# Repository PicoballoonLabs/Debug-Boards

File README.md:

# Debug-Boards

This repository contains the hardware designs for our integrated debug probe, debug adapter, flex debug cables and RF calibration board.

## 📦 Contents

This repository includes designs for:

*   **Flex debug cable**: Flexible flat cable that connects a debugger to the low-profile debug connector on the target board.
*   **Debug Adapter**: SWD debug adapter board that breaks the target debug connector out to a standard debug host, with its own target power supply.
*   **Integrated Debugger**: Integrated debug probe for flashing and debugging target hardware over SWD, with a UART bridge and switchable target power. It is hardware compatible with the [Black Magic Debug](https://black-magic.org/) firmware.
*   **RF VNA calibrator**: Calibration board for vector network analyzer (VNA) RF measurements.

Each subdirectory is a standalone KiCad project with its schematics and PCB layout, and a `production` folder with the manufacturing files (gerbers, BOM, pick-and-place positions) of the released revisions.

The projects use the symbol, footprint and 3D model libraries from [Hardware-Resources](https://github.com/PicoballoonLabs/Hardware-Resources).

## 🔌 Integrated Debugger firmware

No firmware is distributed in this repository. The Integrated Debugger runs the upstream [Black Magic Debug](https://github.com/blackmagic-debug/blackmagic) firmware (GPLv3), which can be installed and updated with [bmputil](https://github.com/blackmagic-debug/bmputil).

The hardware designs in this repository are original work, released under the MIT Licence (see [LICENSE](LICENSE)). They are compatible with Black Magic Debug firmware but are not derived from it.

## 📄 Licence

The hardware designs in this repository are released under the MIT Licence, see [LICENSE](LICENSE).

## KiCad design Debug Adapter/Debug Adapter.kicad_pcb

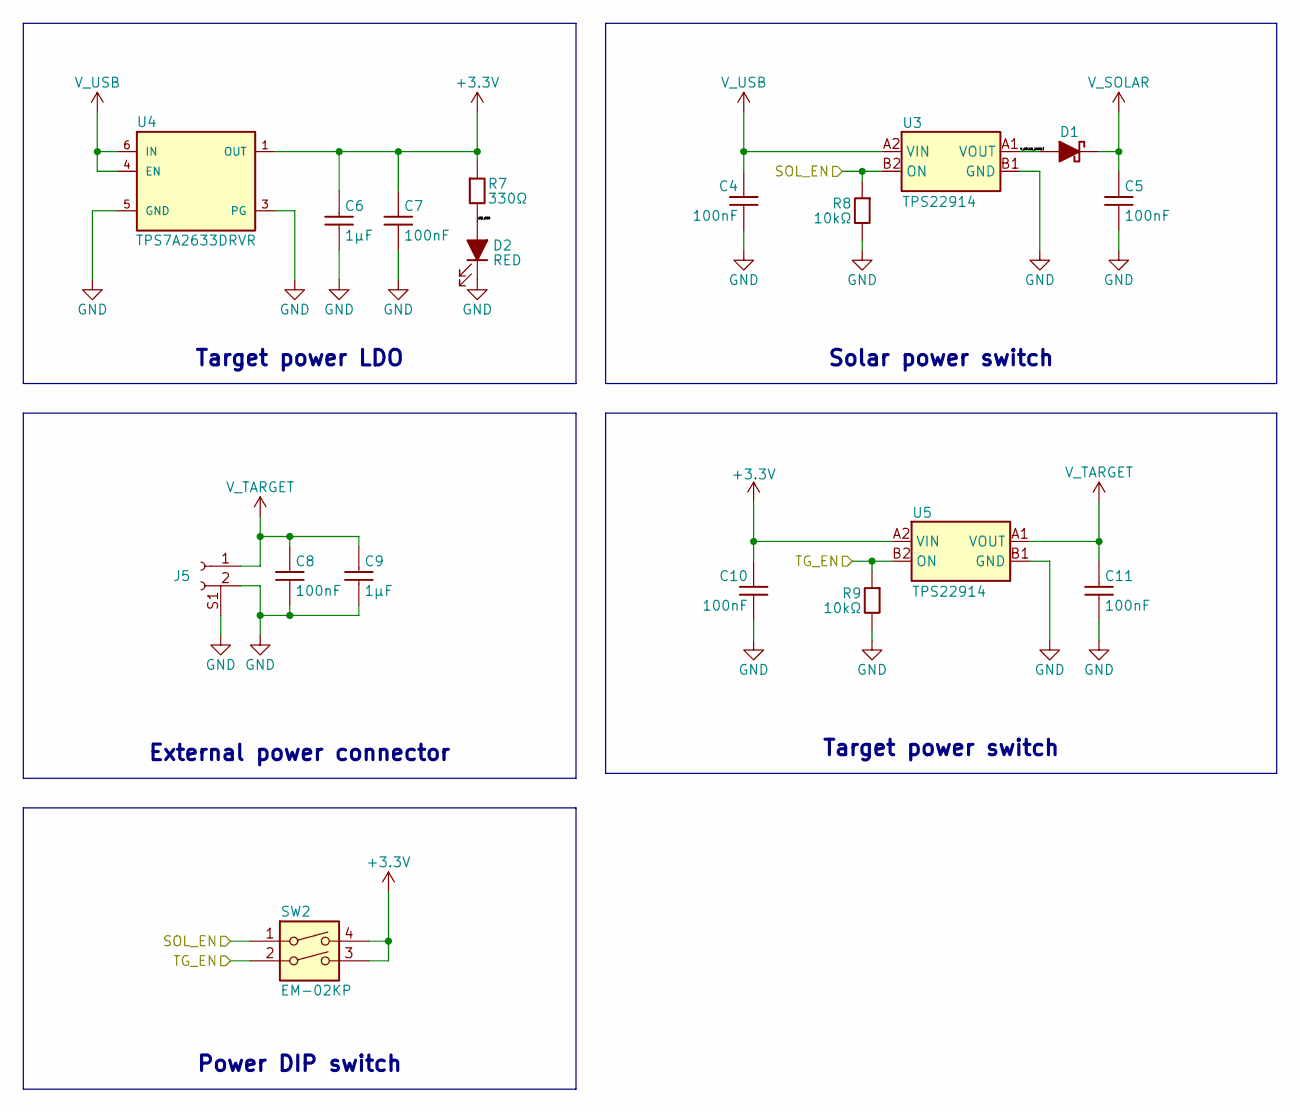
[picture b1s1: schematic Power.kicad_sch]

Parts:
C4, C5, C8, C10, C11: 100nF; Capacitor 0201; MPN GRM033R61A104KE15D; JLCPCB Part # C76934
C6, C9: 1μF; Capacitor 0201; MPN GRM033R60J105MEA2D; JLCPCB Part # C76930
C7: 100nF; Capacitor 0201; MPN GRM033R61A104KE15D; LCSC Part # C76934
D1: PMEG3005EL,315; Diode SOD-882; MPN PMEG3005EL,315; JLCPCB Part # C282565
D2: RED; LED 0603; MPN XL-1608SURC-06; LCSC Part # C965799
J5: PWR; MOLEX 532610271; MPN 532610271; LCSC Part # C177225
R7: 330Ω; Resistor 0201; MPN ERJ1GNF3300C; LCSC Part # C713496
R8, R9: 10kΩ; Resistor 0201; MPN ERJ1GNF1002C; JLCPCB Part # C717002
SW2: EM-02KP; MPN EM-02KP; LCSC Part # C129078
U3, U5: TPS22914; DSBGA-4; MPN TPS22914BYFPR; JLCPCB Part # C1848394
U4: TPS7A2633DRVR; WSON-6 2x2mm; MPN TPS7A2633DRVR; LCSC Part # C2876256

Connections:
+3.3V: C6.1, C7.1, C10.1, R7.1, SW2.3, SW2.4, U4.1 (OUT), U5.A2 (VIN); also elsewhere on the board
/Host/SOL_EN: R8.1, SW2.1, U3.B2 (ON); also elsewhere on the board
/Host/TG_EN: R9.1, SW2.2, U5.B2 (ON); also elsewhere on the board
/Power/LED_REG: D2.1 (K), R7.2
/Power/V_SOLAR_UNFILT: D1.2 (A), U3.A1 (VOUT)
GND: C4.2, C5.2, C6.2, C7.2, C8.2, C9.2, C10.2, C11.2, D2.2 (A), J5.2, J5.S1, J5.S2, R8.2, R9.2, U3.B1 (GND), U4.3 (PG), U4.5 (GND), U4.7 (EXP), U5.B1 (GND); also elsewhere on the board
V_SOLAR: C5.1, D1.1 (K); also elsewhere on the board
V_TARGET: C8.1, C9.1, C11.1, J5.1, U5.A1 (VOUT); also elsewhere on the board
V_USB: C4.1, U3.A2 (VIN), U4.4 (EN), U4.6 (IN); also elsewhere on the board

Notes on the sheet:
Power DIP switch
Target power switch
Solar power switch
External power connector
Target power LDO

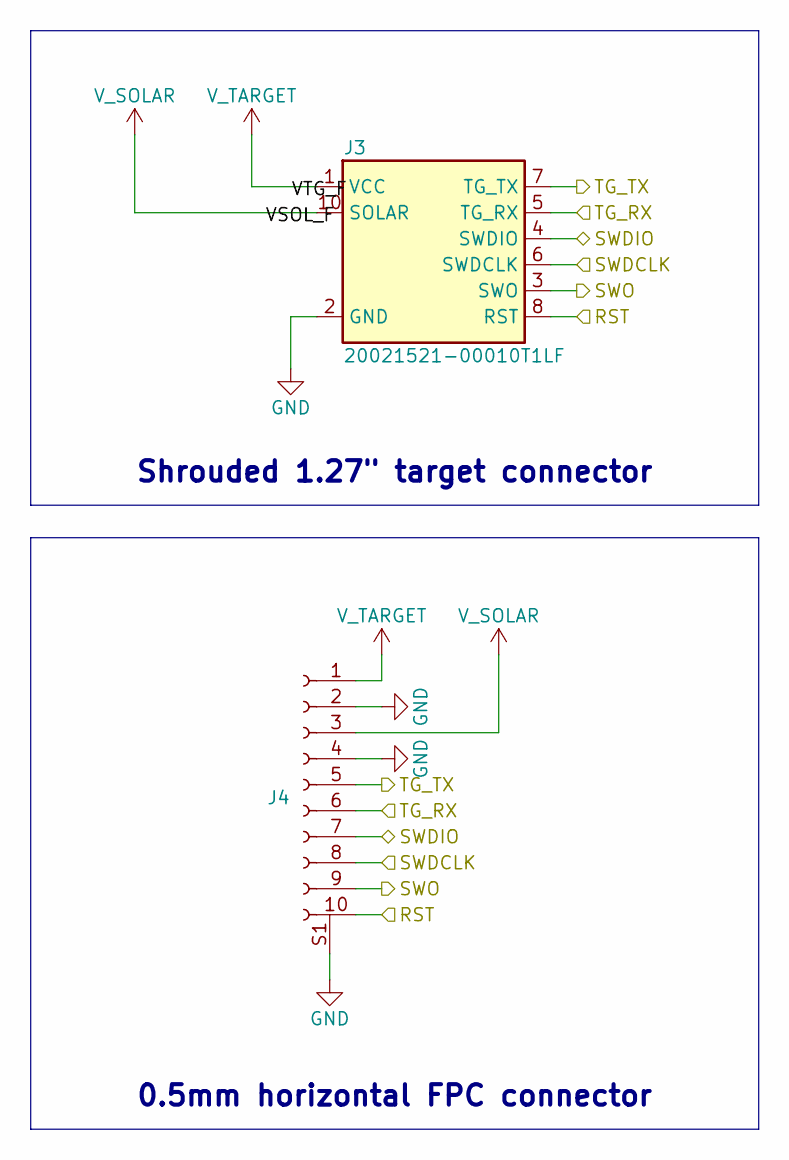
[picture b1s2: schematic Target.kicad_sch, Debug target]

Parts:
J3: 20021521-00010T1LF; MPN 20021521-00010T1LF; LCSC Part # C2972785
J4: FPC socket 10P; FPC connector FPC-05F-10PH20; MPN FPC-05F-10PH20; LCSC Part # C2856798

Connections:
/Host/DEBUG_RX: J3.7 (TG_TX), J4.5; also elsewhere on the board
/Host/DEBUG_TX: J3.5 (TG_RX), J4.6; also elsewhere on the board
/Host/RST: J3.8 (RST), J4.10; also elsewhere on the board
/Host/SWDCLK: J3.6 (SWDCLK), J4.8; also elsewhere on the board
/Host/SWDIO: J3.4 (SWDIO), J4.7; also elsewhere on the board
/Host/SWO: J3.3 (SWO), J4.9; also elsewhere on the board
GND: J3.2 (GND), J3.9 (GND), J4.2, J4.4, J4.S1, J4.S2; also elsewhere on the board
V_SOLAR: J3.10 (SOLAR), J4.3; also elsewhere on the board
V_TARGET: J3.1 (VCC), J4.1; also elsewhere on the board

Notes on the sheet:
Shrouded 1.27{dblquote} target connector
0.5mm horizontal FPC connector

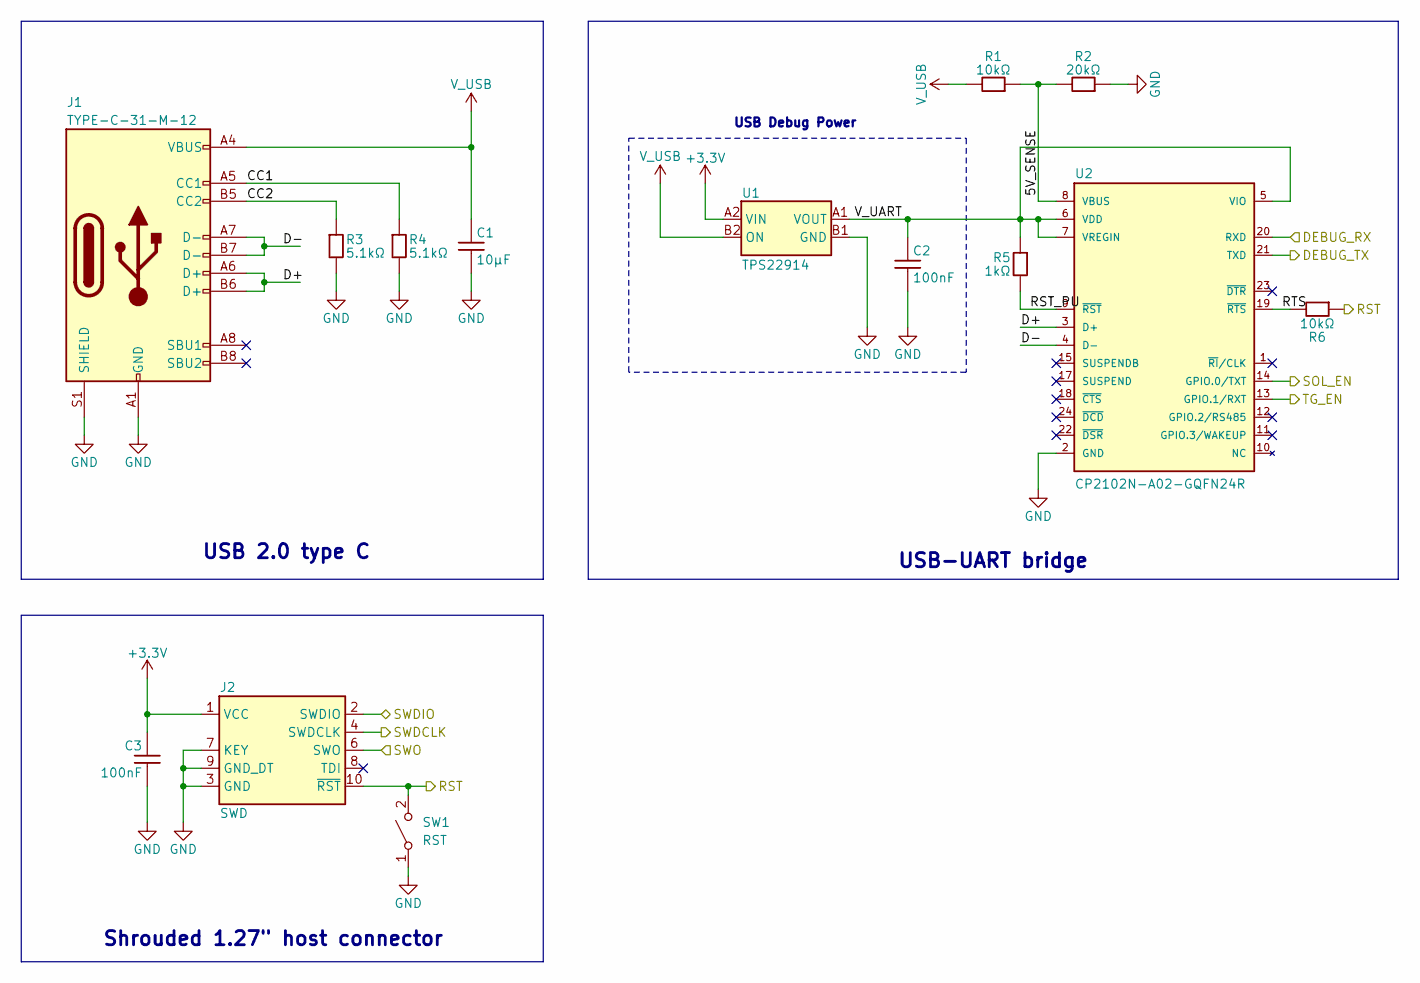
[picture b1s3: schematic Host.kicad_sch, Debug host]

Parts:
C1: 10μF; Capacitor 0402; MPN GRM155R60J106ME44D; JLCPCB Part # C76991
C2, C3: 100nF; Capacitor 0201; MPN GRM033R61A104KE15D; JLCPCB Part # C76934
J1: TYPE-C-31-M-12; MPN TYPE-C-31-M-12; JLCPCB Part # C165948
J2: SWD; 20021521-00010T1LF; MPN 20021521-00010T1LF; LCSC Part # C2972785
R1, R6: 10kΩ; Resistor 0201; MPN ERJ1GNF1002C; JLCPCB Part # C717002
R2: 20kΩ; Resistor 0201; MPN RC0201FR-0720KL; JLCPCB Part # C295787
R3, R4: 5.1kΩ; Resistor 0201; MPN RC0201FR-075K1L; JLCPCB Part # C274341
R5: 1kΩ; Resistor 0201; MPN ERJ1GNF1001C; JLCPCB Part # C717001
SW1: RST; Button GT-TC029B-H025-L1N; MPN GT-TC029B-H025-L1N; LCSC Part # C843669
U1: TPS22914; DSBGA-4; MPN TPS22914BYFPR; JLCPCB Part # C1848394
U2: CP2102N-A02-GQFN24R; QFN-24 4x4mm; MPN CP2102N-A02-GQFN24R; JLCPCB Part # C969151

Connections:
+3.3V: C3.1, J2.1 (VCC), U1.A2 (VIN); also elsewhere on the board
/Host/5V_SENSE: R1.1, R2.2, U2.8 (VBUS)
/Host/CC1: J1.A5 (CC1), R4.1
/Host/CC2: J1.B5 (CC2), R3.1
/Host/D+: J1.A6 (D+), J1.B6 (D+), U2.3 (D+)
/Host/D-: J1.A7 (D-), J1.B7 (D-), U2.4 (D-)
/Host/DEBUG_RX: U2.20 (RXD); also elsewhere on the board
/Host/DEBUG_TX: U2.21 (TXD); also elsewhere on the board
/Host/RST: J2.10 (~RST), R6.1, SW1.2 (B); also elsewhere on the board
/Host/RST_PU: R5.2, U2.9 (~RST)
/Host/RTS: R6.2, U2.19 (~RTS)
/Host/SOL_EN: U2.14 (GPIO.0/TXT); also elsewhere on the board
/Host/SWDCLK: J2.4 (SWDCLK); also elsewhere on the board
/Host/SWDIO: J2.2 (SWDIO); also elsewhere on the board
/Host/SWO: J2.6 (SWO); also elsewhere on the board
/Host/TG_EN: U2.13 (GPIO.1/RXT); also elsewhere on the board
/Host/V_UART: C2.1, R5.1, U1.A1 (VOUT), U2.5 (VIO), U2.6 (VDD), U2.7 (VREGIN)
GND: C1.2, C2.2, C3.2, J1.A1 (GND), J1.A12 (GND), J1.B1 (GND), J1.B12 (GND), J1.S1 (SHIELD), J1.S2 (SHIELD), J1.S3 (SHIELD), J1.S4 (SHIELD), J2.3 (GND), J2.5 (GND), J2.7 (KEY), J2.9 (GND_DT), R2.1, R3.2, R4.2, SW1.1 (A), U1.B1 (GND), U2.2 (GND), U2.25 (GND); also elsewhere on the board
V_USB: C1.1, J1.A4 (VBUS), J1.A9 (VBUS), J1.B4 (VBUS), J1.B9 (VBUS), R1.2, U1.B2 (ON); also elsewhere on the board

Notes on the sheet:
USB-UART bridge
Shrouded 1.27{dblquote} host connector
USB Debug Power
USB 2.0 type C

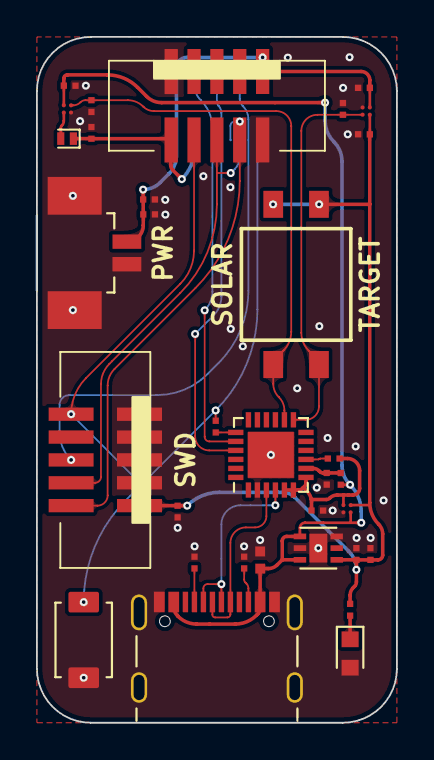
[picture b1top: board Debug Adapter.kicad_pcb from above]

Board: 2 copper layers, 20.0 x 38.1 mm, 34 parts (1 on the bottom side), 23 nets.

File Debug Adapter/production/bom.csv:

Designator,Footprint,Quantity,Value,LCSC Part #
C1,Capacitor 0402,1,10μF,C76991
"C10, C11, C2, C3, C4, C5, C7, C8",Capacitor 0201,8,100nF,C76934
"C6, C9",Capacitor 0201,2,1μF,C76930
D1,Diode SOD-882,1,"PMEG3005EL,315",C282565
D2,LED 0603,1,RED,C965799
J1,TYPE-C-31-M-12,1,TYPE-C-31-M-12,C165948
J2,20021521-00010T1LF,1,SWD,C2972785
J3,20021521-00010T1LF,1,20021521-00010T1LF,C2972785
J4,FPC connector FPC-05F-10PH20,1,FPC socket 10P,C2856798
J5,MOLEX 532610271,1,PWR,C177225
"R1, R6, R8, R9",Resistor 0201,4,10kΩ,C717002
R2,Resistor 0201,1,20kΩ,C295787
"R3, R4",Resistor 0201,2,5.1kΩ,C274341
R5,Resistor 0201,1,1kΩ,C717001
R7,Resistor 0201,1,330Ω,C713496
SW1,Button GT-TC029B-H025-L1N,1,RST,C843669
SW2,EM-02KP,1,EM-02KP,C129078
"U1, U3, U5",DSBGA-4,3,TPS22914,C1848394
U2,QFN-24 4x4mm,1,CP2102N-A02-GQFN24R,C969151
U4,WSON-6 2x2mm,1,TPS7A2633DRVR,C2876256

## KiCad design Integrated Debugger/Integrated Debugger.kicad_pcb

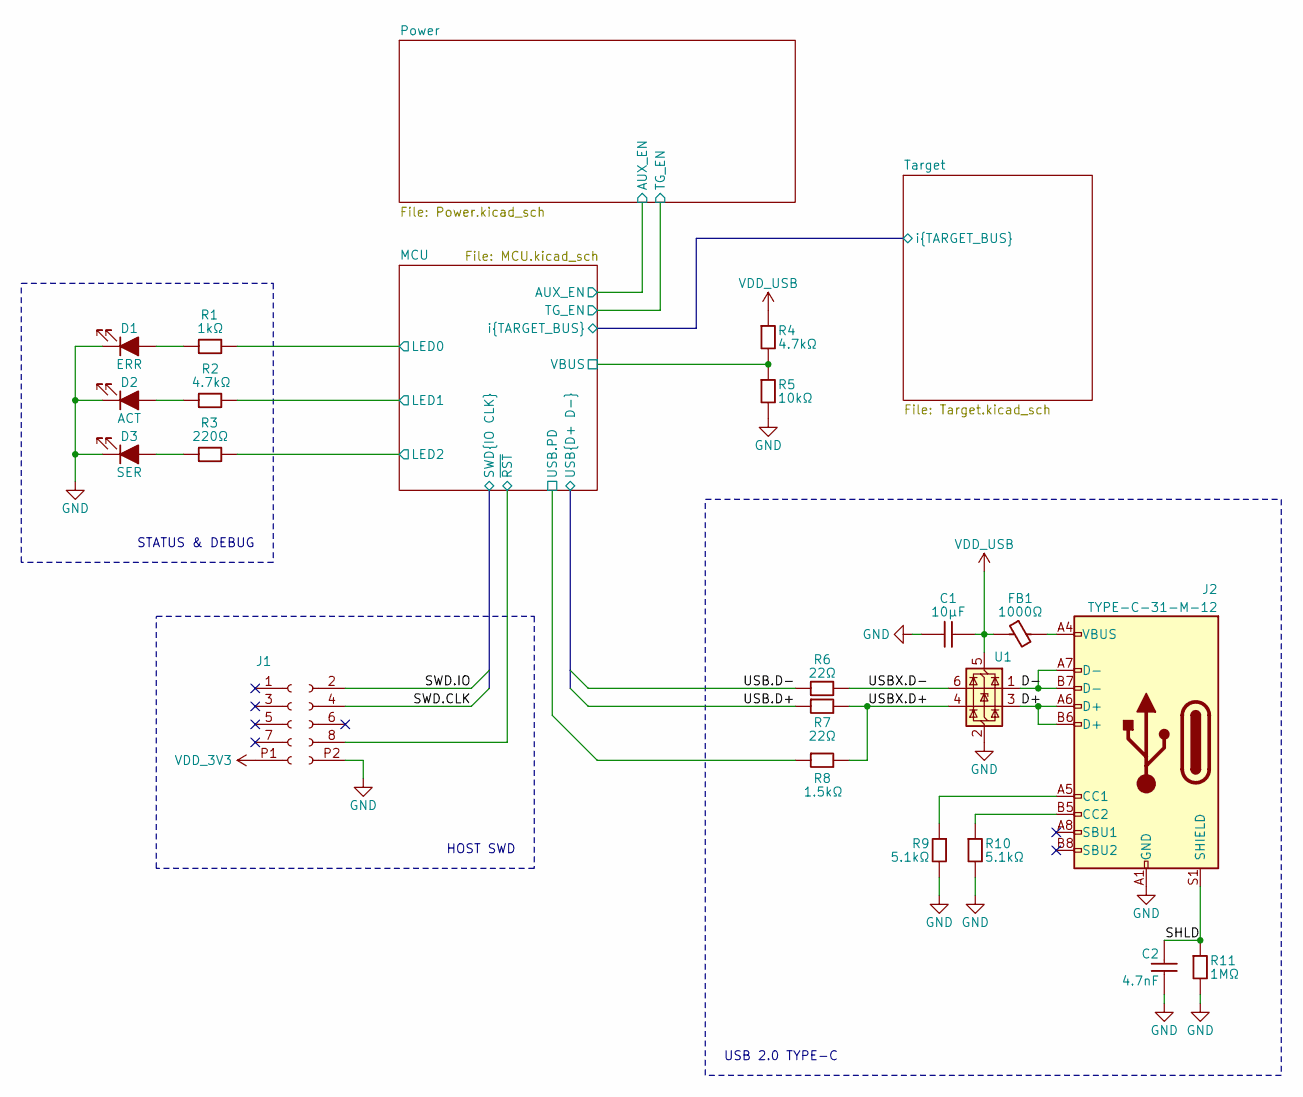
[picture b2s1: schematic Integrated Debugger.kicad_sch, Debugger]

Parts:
C1: 10μF; Capacitor 0402; MPN CL05A106MP5NUNC; LCSC Part # C315248
C2: 4.7nF; Capacitor 0603; MPN CC0603KRX7RABB472; LCSC Part # C596328
D1: ERR; LED 0402; MPN APHHS1005SURCK; LCSC Part # C2852592
D2: ACT; LED 0402; MPN APHHS1005LZGCK-V; LCSC Part # C5875752
D3: SER; LED 0402; MPN APHHS1005LQBC/D-V; LCSC Part # C5354973
FB1: 1000Ω; Inductor 0402; MPN BLM15HD102SN1D; LCSC Part # C21516
J1: B2B GT-B0353FSV06-08B0201; B2B GT-B0353MSV04-08B0201; MPN GT-B0353MSV04-08B0201; LCSC Part # C42385857
J2: TYPE-C-31-M-12; MPN TYPE-C-31-M-12; LCSC Part # C165948
R1: 1kΩ; Resistor 0201; MPN RC0201FR-071KL; LCSC Part # C138165
R2, R4: 4.7kΩ; Resistor 0201; MPN RC0201FR-074K7L; LCSC Part # C138135
R3: 220Ω; Resistor 0201; MPN AC0201JR-07220RL; LCSC Part # C226657
R5: 10kΩ; Resistor 0201; MPN ERJ1GNF1002C; LCSC Part # C717002
R6, R7: 22Ω; Resistor 0201; MPN RC0201FR-0722RL; LCSC Part # C155743
R8: 1.5kΩ; Resistor 0201; MPN RC0201FR-071K5L; LCSC Part # C155737
R9, R10: 5.1kΩ; Resistor 0201; MPN 0201WMF5101TEE; LCSC Part # C270344
R11: 1MΩ; Resistor 0603; MPN ESR03EZPJ105; LCSC Part # ESR03EZPJ105
U1: USBLC6-2P6; XSON-6; MPN USBULC6-2M6; LCSC Part # C2999115

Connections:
/D+: J2.A6 (D+), J2.B6 (D+), U1.3 (I/O2)
/D-: J2.A7 (D-), J2.B7 (D-), U1.1 (I/O1)
/MCU/LED0: R1.2; also elsewhere on the board
/MCU/LED1: R2.2; also elsewhere on the board
/MCU/LED2: R3.2; also elsewhere on the board
/MCU/SWD.CLK: J1.4; also elsewhere on the board
/MCU/SWD.IO: J1.2; also elsewhere on the board
/MCU/USB.D+: R7.1; also elsewhere on the board
/MCU/USB.D-: R6.1; also elsewhere on the board
/MCU/USB.PD: R8.1; also elsewhere on the board
/MCU/VBUS: R4.2, R5.1; also elsewhere on the board
/MCU/~RST: J1.8; also elsewhere on the board
/SHLD: C2.1, J2.S1 (SHIELD), J2.S2 (SHIELD), J2.S3 (SHIELD), J2.S4 (SHIELD), R11.1
/USBX.D+: R7.2, R8.2, U1.4 (I/O2)
/USBX.D-: R6.2, U1.6 (I/O1)
GND: C1.2, C2.2, D1.2 (A), D2.2 (A), D3.2 (A), J1.P2 (Pin_10), J1.P2_2 (Pin_10), J2.A1 (GND), J2.A12 (GND), J2.B1 (GND), J2.B12 (GND), R5.2, R9.2, R10.2, R11.2, U1.2 (GND); also elsewhere on the board
unnamed: D1.1 (K), R1.1
unnamed: D2.1 (K), R2.1
unnamed: D3.1 (K), R3.1
unnamed: FB1.2, J2.A4 (VBUS), J2.A9 (VBUS), J2.B4 (VBUS), J2.B9 (VBUS)
unnamed: J2.A5 (CC1), R9.1
unnamed: J2.B5 (CC2), R10.1
VDD_3V3: J1.P1 (Pin_9), J1.P1_2 (Pin_9); also elsewhere on the board
VDD_USB: C1.1, FB1.1, R4.1, U1.5 (VBUS); also elsewhere on the board

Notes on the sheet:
USB 2.0 TYPE-C
HOST SWD
STATUS & DEBUG

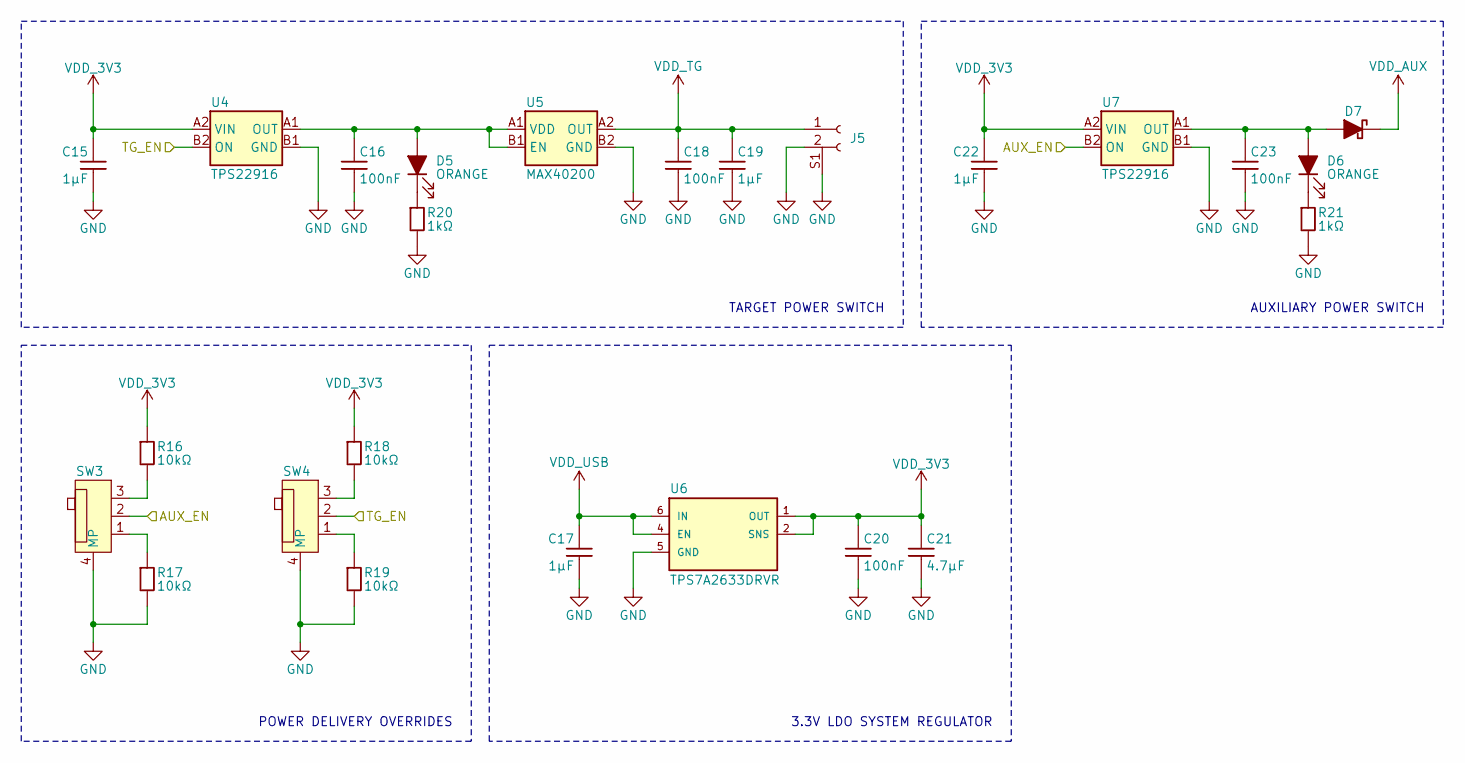
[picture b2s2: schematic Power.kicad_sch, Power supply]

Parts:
C15, C22: 1µF; Capacitor 0201; MPN GRM033R61C105ME15D; LCSC Part # C335102
C16, C18, C20, C23: 100nF; Capacitor 0201; MPN GRM033R6YA104KE14D; LCSC Part # C181043
C17, C19: 1μF; Capacitor 0201; MPN GRM033R61C105ME15D; LCSC Part # C335102
C21: 4.7μF; Capacitor 0201; MPN GRM035R60J475ME15D; LCSC Part # C335103
D5, D6: ORANGE; LED 0402; MPN APHHS1005SECK; LCSC Part # C5875753
D7: CFSH05-20L TR PBFREE; Diode SOD-882; MPN CFSH05-20L TR PBFREE; LCSC Part # C5258921
J5: PWR; JST-SH-2P; MPN SM02B-SRSS-TB(LF)(SN); LCSC Part # C160402
R16, R17, R18, R19: 10kΩ; Resistor 0201; MPN ERJ1GNF1002C; LCSC Part # C717002
R20, R21: 1kΩ; Resistor 0201; MPN RC0201FR-071KL; LCSC Part # C138165
SW3: AUXILIARY POWER; Switch MINI MSK12CO2; MPN MINI MSK12CO2; LCSC Part # C2681570
SW4: Target Override; Switch MINI MSK12CO2; MPN MINI MSK12CO2; LCSC Part # C2681570
U4, U7: TPS22916; DSBGA-4; MPN TPS22916CNLYFPR; LCSC Part # C3230035
U5: MAX40200; WLP-4; MPN MAX40200ANS+T; LCSC Part # C3227637
U6: TPS7A2633DRVR; WSON-6 2x2mm; MPN TLV76733DRVR; LCSC Part # C2848334

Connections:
/MCU/AUX_EN: SW3.2, U7.B2 (ON); also elsewhere on the board
/MCU/TG_EN: SW4.2, U4.B2 (ON); also elsewhere on the board
GND: C15.2, C16.2, C17.2, C18.2, C19.2, C20.2, C21.2, C22.2, C23.2, J5.2, J5.S1, J5.S2, R17.2, R19.2, R20.2, R21.2, SW3.4 (MP), SW4.4 (MP), U4.B1 (GND), U5.B2 (GND), U6.3 (GND), U6.5 (GND), U6.7 (EXP), U7.B1 (GND); also elsewhere on the board
unnamed: D5.2 (A), R20.1
unnamed: C16.1, D5.1 (K), U4.A1 (OUT), U5.A1 (VDD), U5.B1 (EN)
unnamed: D6.2 (A), R21.1
unnamed: C23.1, D6.1 (K), D7.2 (A), U7.A1 (OUT)
unnamed: R16.2, SW3.3
unnamed: R17.1, SW3.1
unnamed: R18.2, SW4.3
unnamed: R19.1, SW4.1
VDD_3V3: C15.1, C20.1, C21.1, C22.1, R16.1, R18.1, U4.A2 (VIN), U6.1 (OUT), U6.2 (SNS), U7.A2 (VIN); also elsewhere on the board
VDD_AUX: D7.1 (K); also elsewhere on the board
VDD_TG: C18.1, C19.1, J5.1, U5.A2 (OUT); also elsewhere on the board
VDD_USB: C17.1, U6.4 (EN), U6.6 (IN); also elsewhere on the board

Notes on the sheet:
POWER DELIVERY OVERRIDES
AUXILIARY POWER SWITCH
TARGET POWER SWITCH
3.3V LDO SYSTEM REGULATOR

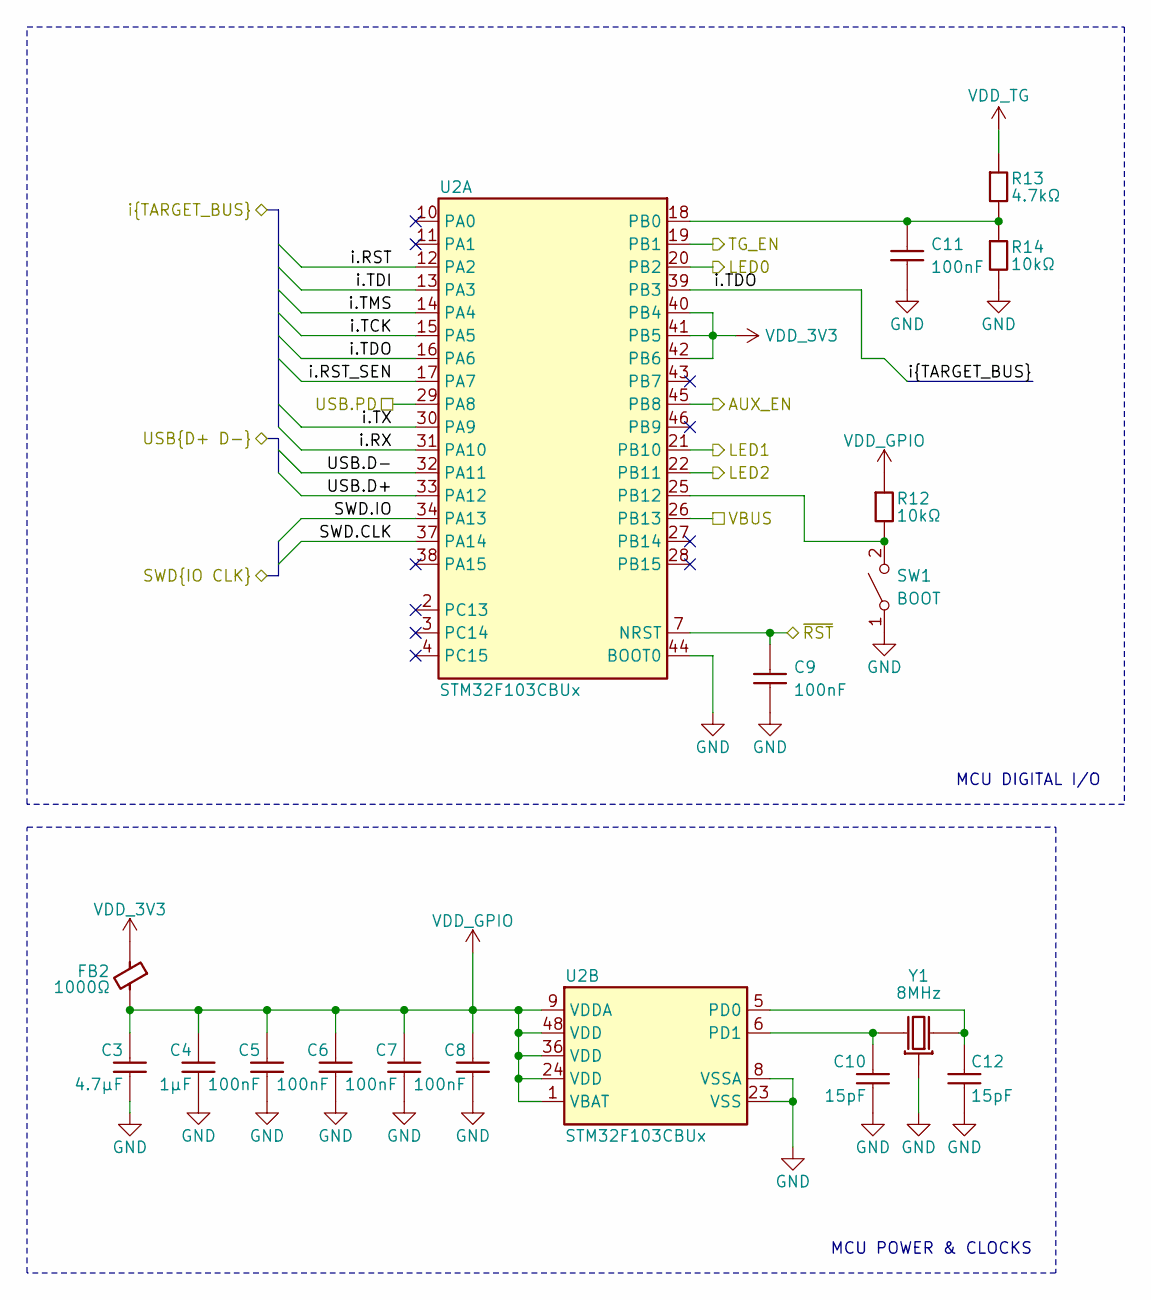
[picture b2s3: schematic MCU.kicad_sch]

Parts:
C3: 4.7μF; Capacitor 0201; MPN GRM035R60J475ME15D; LCSC Part # C335103
C4: 1μF; Capacitor 0201; MPN GRM033R61C105ME15D; LCSC Part # C335102
C5, C6, C7, C8, C9, C11: 100nF; Capacitor 0201; MPN GRM033R6YA104KE14D; LCSC Part # C181043
C10, C12: 15pF; Capacitor 0201; MPN CC0201GRNPO8BN150; LCSC Part # C1853525
FB2: 1000Ω; Inductor 0402; MPN BLM15HD102SN1D; LCSC Part # C21516
R12, R14: 10kΩ; Resistor 0201; MPN ERJ1GNF1002C; LCSC Part # C717002
R13: 4.7kΩ; Resistor 0201; MPN RC0201FR-074K7L; LCSC Part # C138135
SW1: BOOT; Button SMD-4P,2.5x1.6mm; MPN HX TS152605A 160gf; LCSC Part # C25168822
U2: STM32F103CBUx; QFN-48 7x7mm; MPN STM32F103CBU6; LCSC Part # C55506
Y1: 8MHz; Crystal 3225; MPN 1C208000BC0R; LCSC Part # C57131

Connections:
/MCU/AUX_EN: U2.45 (PB8); also elsewhere on the board
/MCU/LED0: U2.20 (PB2); also elsewhere on the board
/MCU/LED1: U2.21 (PB10); also elsewhere on the board
/MCU/LED2: U2.22 (PB11); also elsewhere on the board
/MCU/SWD.CLK: U2.37 (PA14); also elsewhere on the board
/MCU/SWD.IO: U2.34 (PA13); also elsewhere on the board
/MCU/TG_EN: U2.19 (PB1); also elsewhere on the board
/MCU/USB.D+: U2.33 (PA12); also elsewhere on the board
/MCU/USB.D-: U2.32 (PA11); also elsewhere on the board
/MCU/USB.PD: U2.29 (PA8); also elsewhere on the board
/MCU/VBUS: U2.26 (PB13); also elsewhere on the board
/MCU/i.RST: U2.12 (PA2); also elsewhere on the board
/MCU/i.RST_SEN: U2.17 (PA7); also elsewhere on the board
/MCU/i.RX: U2.31 (PA10); also elsewhere on the board
/MCU/i.TCK: U2.15 (PA5); also elsewhere on the board
/MCU/i.TDI: U2.13 (PA3); also elsewhere on the board
/MCU/i.TDO: U2.16 (PA6), U2.39 (PB3); also elsewhere on the board
/MCU/i.TMS: U2.14 (PA4); also elsewhere on the board
/MCU/i.TX: U2.30 (PA9); also elsewhere on the board
/MCU/~RST: C9.2, U2.7 (NRST); also elsewhere on the board
GND: C3.1, C4.1, C5.1, C6.1, C7.1, C8.1, C9.1, C10.1, C11.1, C12.1, R14.2, SW1.1 (A), U2.8 (VSSA), U2.23 (VSS), U2.35 (VSS), U2.44 (BOOT0), U2.47 (VSS), U2.49 (VSS), Y1.2, Y1.4; also elsewhere on the board
unnamed: R12.2, SW1.2 (B), U2.25 (PB12)
unnamed: C11.2, R13.2, R14.1, U2.18 (PB0)
unnamed: C12.2, U2.5 (PD0), Y1.1
unnamed: C10.2, U2.6 (PD1), Y1.3
VDD_3V3: FB2.1, U2.40 (PB4), U2.41 (PB5), U2.42 (PB6); also elsewhere on the board
VDD_GPIO: C3.2, C4.2, C5.2, C6.2, C7.2, C8.2, FB2.2, R12.1, U2.1 (VBAT), U2.9 (VDDA), U2.24 (VDD), U2.36 (VDD), U2.48 (VDD)
VDD_TG: R13.1; also elsewhere on the board

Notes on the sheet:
MCU DIGITAL I/O
MCU POWER & CLOCKS

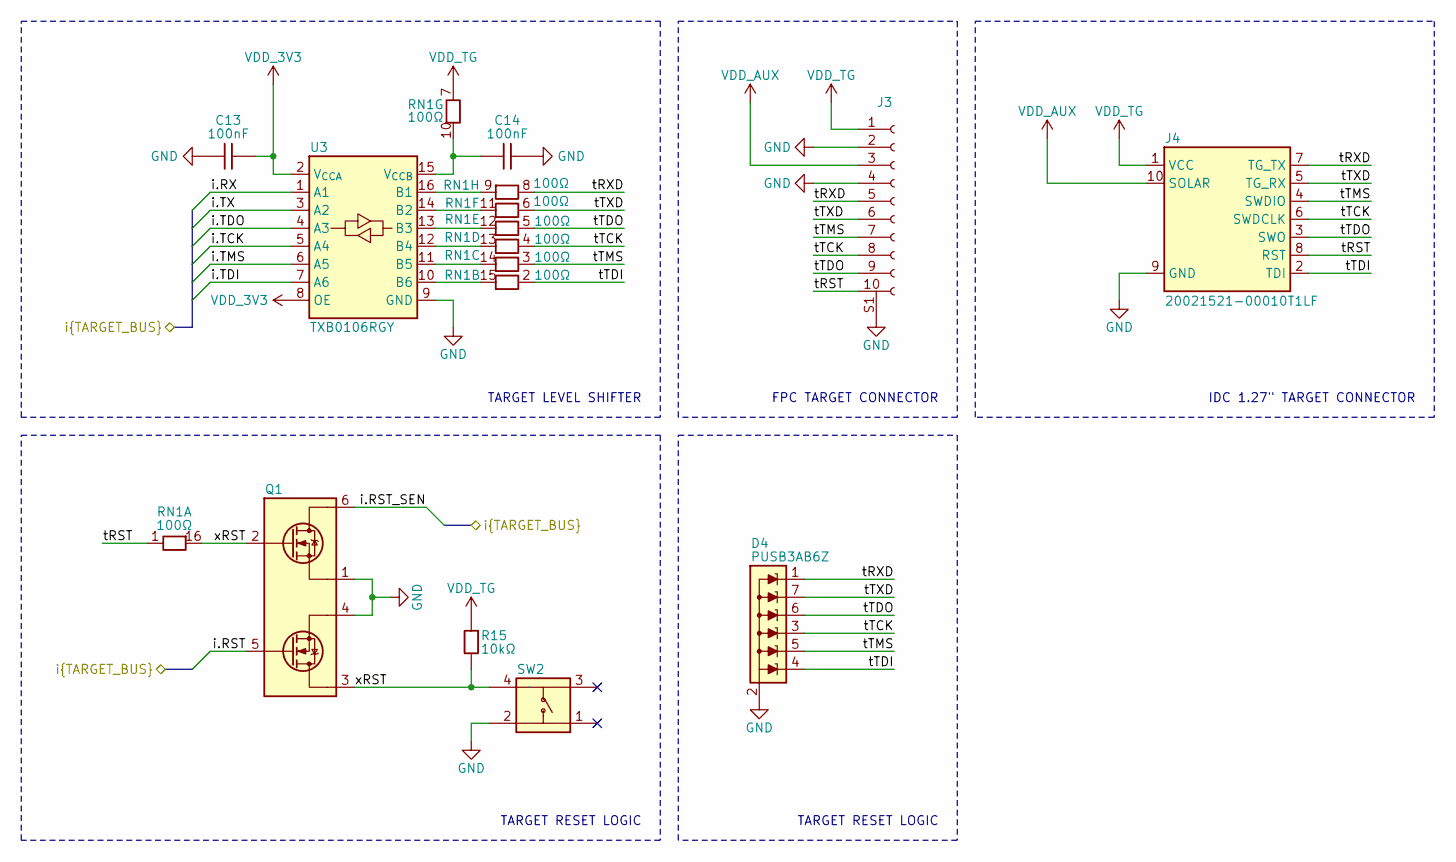
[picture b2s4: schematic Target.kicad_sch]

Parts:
C13, C14: 100nF; Capacitor 0201; MPN GRM033R6YA104KE14D; LCSC Part # C181043
D4: PUSB3AB6Z; XSON-7; MPN PUSB3AB6Z; LCSC Part # C553550
J3: FPC socket 10P; FH28-10S-0.5SH(05); MPN FH28-10S-0.5SH(05); LCSC Part # C598018
J4: 20021521-00010T1LF; MPN 20021521-00010C1LF; LCSC Part # C598547
Q1: DMN31D5UDA-7B; X2-DFN0806-6; MPN DMN2991UDA-7B; LCSC Part # C2937136
R15: 10kΩ; Resistor 0201; MPN ERJ1GNF1002C; LCSC Part # C717002
RN1: 100Ω; Resistor 0402x8; MPN YC248-JR-07100RL; LCSC Part # C695200
SW2: RESET; SMD-4P 4.2x3.2mm; MPN YTS1T0161AWJ00; LCSC Part # C2985732
U3: TXB0106RGY; PVQFN-N16; MPN TXB0106RGY; LCSC Part # C2652978

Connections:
/MCU/i.RST: Q1.5; also elsewhere on the board
/MCU/i.RST_SEN: Q1.6; also elsewhere on the board
/MCU/i.RX: U3.1 (A1); also elsewhere on the board
/MCU/i.TCK: U3.5 (A4); also elsewhere on the board
/MCU/i.TDI: U3.7 (A6); also elsewhere on the board
/MCU/i.TDO: U3.4 (A3); also elsewhere on the board
/MCU/i.TMS: U3.6 (A5); also elsewhere on the board
/MCU/i.TX: U3.3 (A2); also elsewhere on the board
/Target/tRST: J3.10, J4.8 (RST), RN1.1 (R1.1)
/Target/tRXD: D4.1 (K), J3.5, J4.7 (TG_TX), RN1.8 (R8.1)
/Target/tTCK: D4.3 (K), J3.8, J4.6 (SWDCLK), RN1.4 (R4.1)
/Target/tTDI: D4.4 (K), J4.2 (TDI), RN1.2 (R2.1)
/Target/tTDO: D4.6 (K), J3.9, J4.3 (SWO), RN1.5 (R5.1)
/Target/tTMS: D4.5 (K), J3.7, J4.4 (SWDIO), RN1.3 (R3.1)
/Target/tTXD: D4.7 (K), J3.6, J4.5 (TG_RX), RN1.6 (R6.1)
/Target/xRST: Q1.2, Q1.3, R15.2, RN1.16 (R1.2), SW2.4
GND: C13.2, C14.2, D4.2 (A), J3.2, J3.4, J3.S1, J3.S2, J4.9 (GND), Q1.1, Q1.4, SW2.2, U3.9 (GND), U3.17 (GND); also elsewhere on the board
unnamed: RN1.15 (R2.2), U3.10 (B6)
unnamed: RN1.14 (R3.2), U3.11 (B5)
unnamed: RN1.13 (R4.2), U3.12 (B4)
unnamed: RN1.12 (R5.2), U3.13 (B3)
unnamed: RN1.11 (R6.2), U3.14 (B2)
unnamed: C14.1, RN1.10 (R7.2), U3.15 (V_{CCB})
unnamed: RN1.9 (R8.2), U3.16 (B1)
VDD_3V3: C13.1, U3.2 (V_{CCA}), U3.8 (OE); also elsewhere on the board
VDD_AUX: J3.3, J4.10 (SOLAR); also elsewhere on the board
VDD_TG: J3.1, J4.1 (VCC), R15.1, RN1.7 (R7.1); also elsewhere on the board

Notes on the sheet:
TARGET RESET LOGIC
IDC 1.27{dblquote} TARGET CONNECTOR
FPC TARGET CONNECTOR
TARGET LEVEL SHIFTER

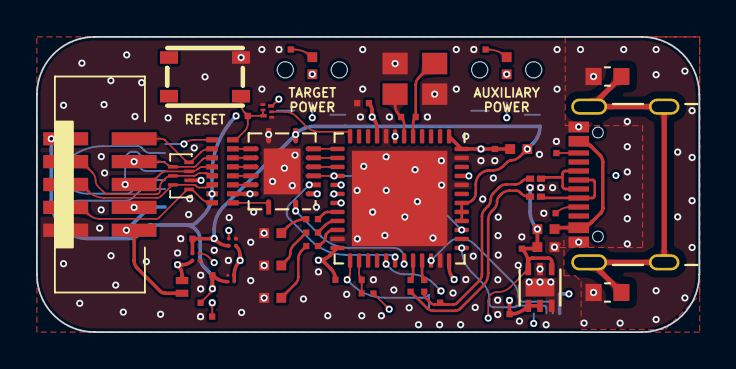
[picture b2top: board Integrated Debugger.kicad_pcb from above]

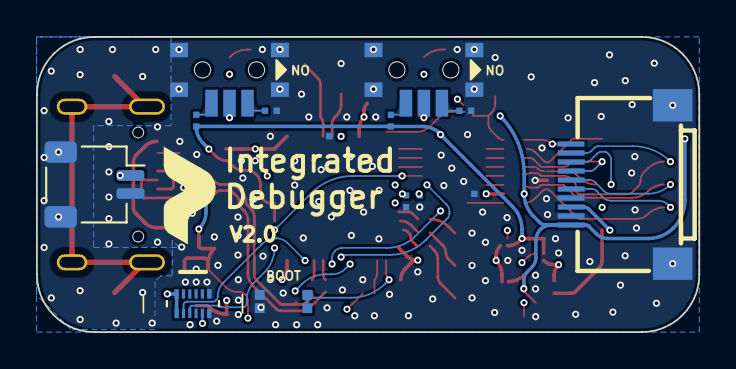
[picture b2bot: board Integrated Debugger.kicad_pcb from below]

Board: 6 copper layers, 36.8 x 16.4 mm, 72 parts (14 on the bottom side), 64 nets.

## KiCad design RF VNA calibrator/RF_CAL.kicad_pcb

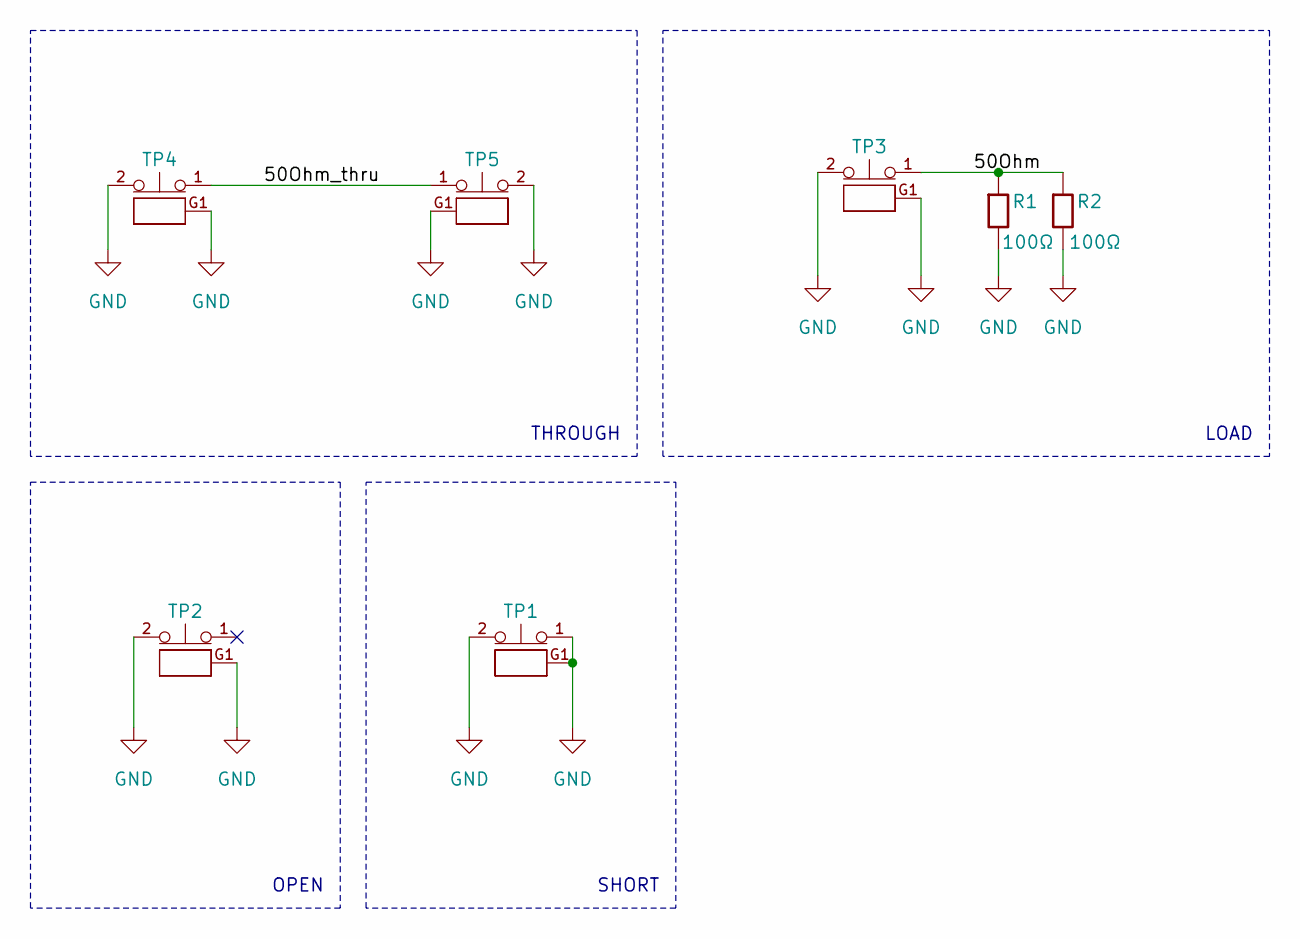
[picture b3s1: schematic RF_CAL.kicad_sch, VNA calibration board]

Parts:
R1, R2: 100Ω; Resistor 0603; LCSC Part # C160603
TP1, TP2, TP3, TP4, TP5: Coaxial Testpoint; MM8030-2610RK0; MPN MM8030-2610RK0; LCSC Part # MM8030-2610RK0

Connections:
/50Ohm: R1.1, R2.1, TP3.1 (IN)
/50Ohm_thru: TP4.1 (IN), TP5.1 (IN)
GND: R1.2, R2.2, TP1.1 (IN), TP1.2 (OUT), TP1.G1 (GND), TP1.G2 (GND), TP2.2 (OUT), TP2.G1 (GND), TP2.G2 (GND), TP3.2 (OUT), TP3.G1 (GND), TP3.G2 (GND), TP4.2 (OUT), TP4.G1 (GND), TP4.G2 (GND), TP5.2 (OUT), TP5.G1 (GND), TP5.G2 (GND)

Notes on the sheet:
THROUGH
LOAD
OPEN
SHORT

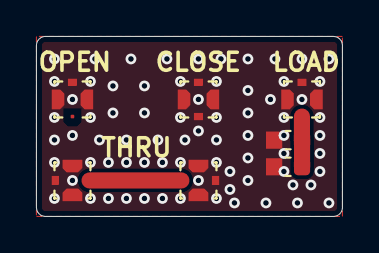
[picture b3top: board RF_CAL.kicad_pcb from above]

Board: 2 copper layers, 17.0 x 10.0 mm, 7 parts (0 on the bottom side), 3 nets.

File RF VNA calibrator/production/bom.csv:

Designator,Footprint,Quantity,Value,LCSC Part #
"R1, R2",Resistor 0603,2,100Ω,C160603
"TP1, TP2, TP3, TP4, TP5",MM8030-2610RK0,5,Coaxial Testpoint,C91632
